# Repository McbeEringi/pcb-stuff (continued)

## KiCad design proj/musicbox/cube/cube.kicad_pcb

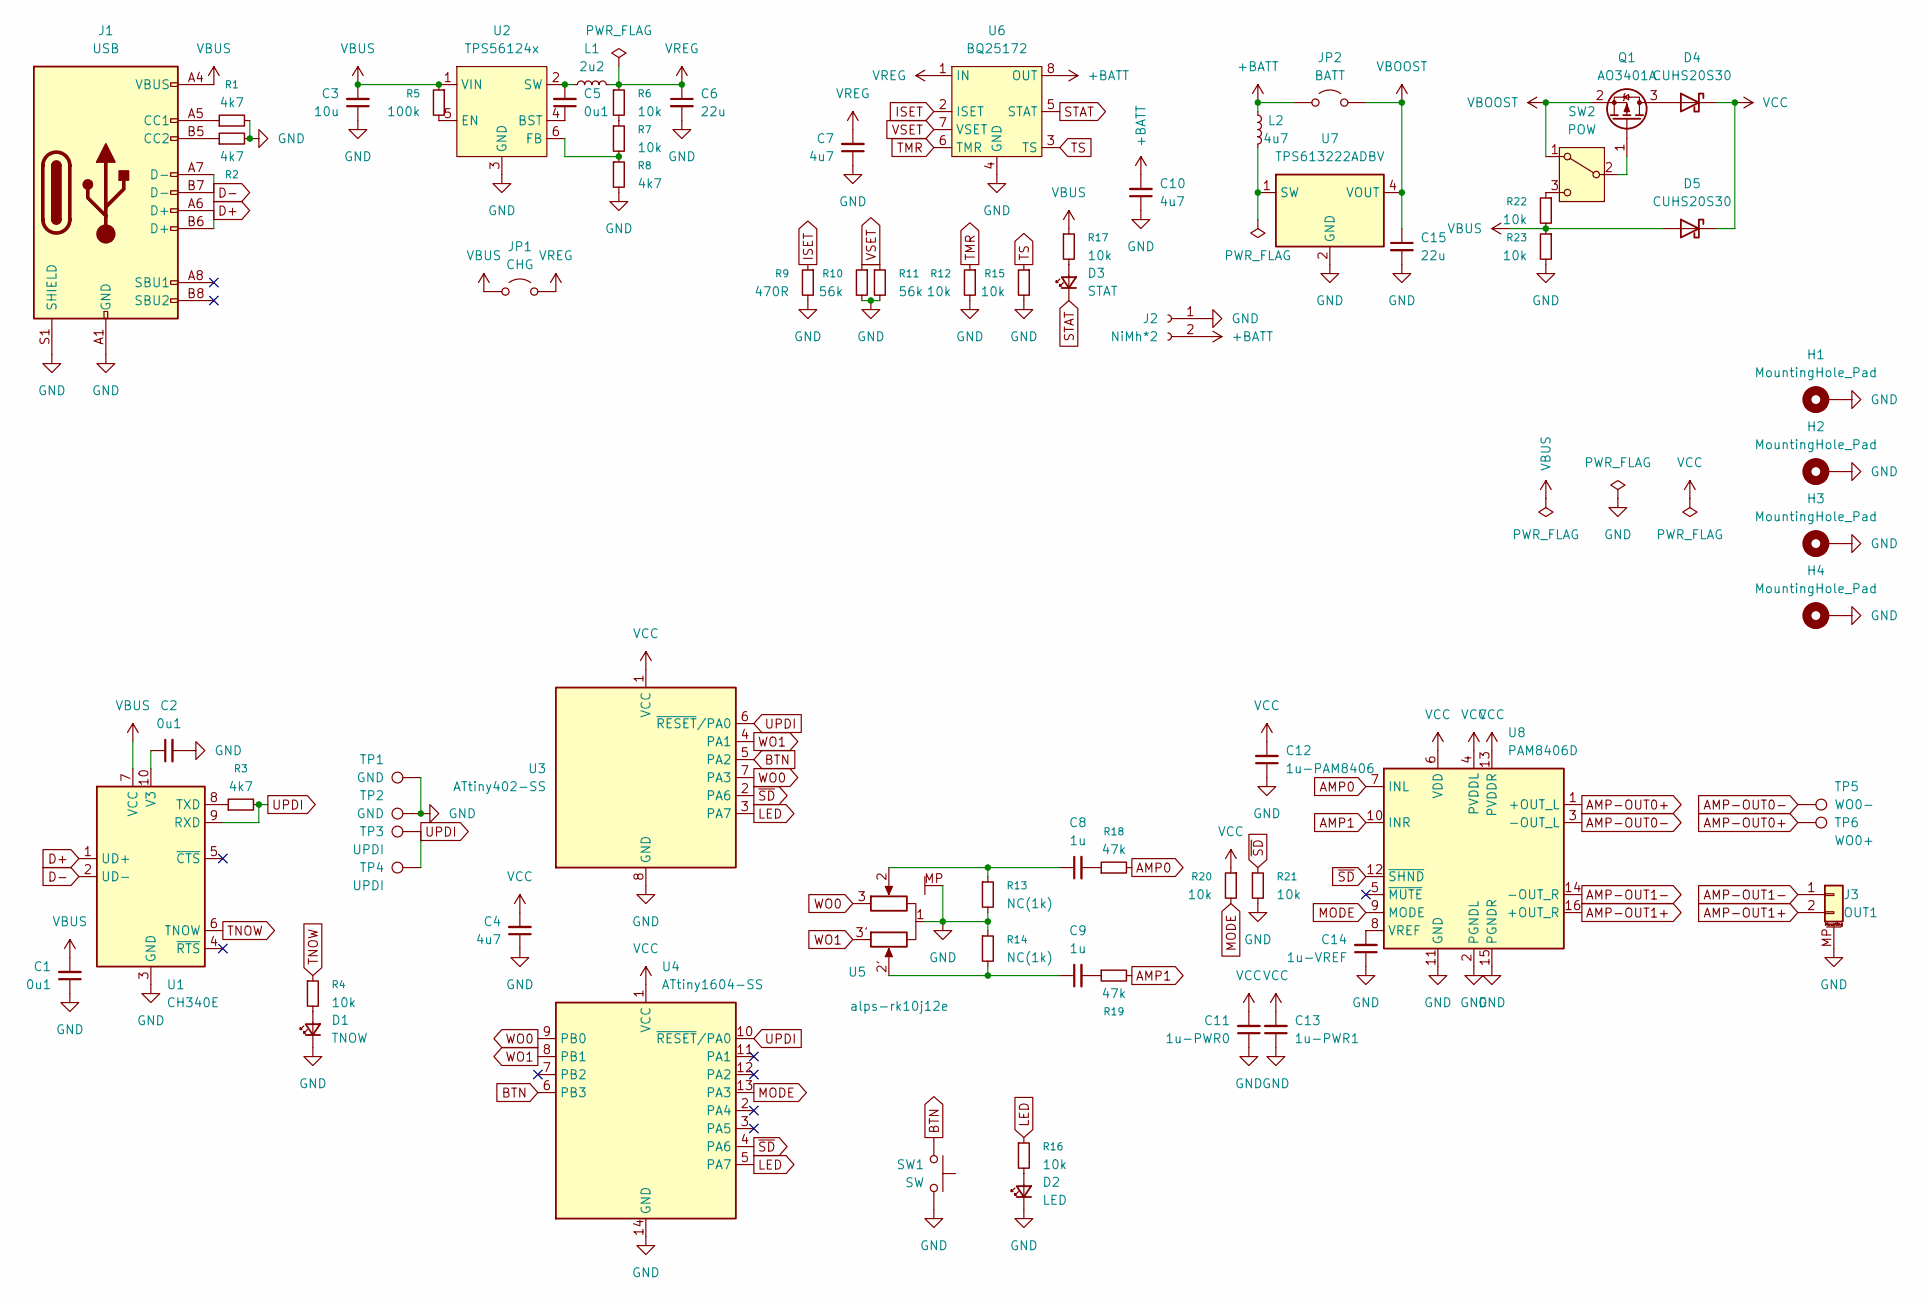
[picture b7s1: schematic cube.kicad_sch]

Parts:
C1, C2, C5: 0u1; C_0603_1608Metric
C3: 10u; C_0603_1608Metric
C4, C7, C10: 4u7; C_0603_1608Metric
C6, C15: 22u; C_0603_1608Metric
C8, C9: 1u; C_0603_1608Metric
C11: 1u-PWR0; C_0603_1608Metric
C12: 1u-PAM8406; C_0603_1608Metric
C13: 1u-PWR1; C_0603_1608Metric
C14: 1u-VREF; C_0603_1608Metric
D1: TNOW; LED_0603_1608Metric
D2: LED; LED_0603_1608Metric
D3: STAT; LED_0603_1608Metric
D4, D5: CUHS20S30; US2H
H1, H2, H3, H4: MountingHole_Pad; MountingHole_3.2mm_M3_Pad
J1: USB; USB_C_Receptacle_GCT_USB4105-xx-A_16P_TopMnt_Horizontal
J2: NiMh*2; JST_XH_B2B-XH-A_1x02_P2.50mm_Vertical
J3: OUT1; JST_ZH_S2B-ZR-SM4A-TF_1x02-1MP_P1.50mm_Horizontal
JP1: CHG; R_0603_1608Metric
JP2: BATT; R_0603_1608Metric
L1: 2u2; L_0805_2012Metric
L2: 4u7; L_1008_2520Metric
Q1: AO3401A; SOT-23
R1, R2, R3, R8: 4k7; R_0603_1608Metric
R4, R6, R7, R12, R15, R16, R17, R20, R21, R22, R23: 10k; R_0603_1608Metric
R5: 100k; R_0603_1608Metric
R9: 470R; R_0603_1608Metric
R10, R11: 56k; R_0603_1608Metric
R13, R14: NC(1k); R_0603_1608Metric
R18, R19: 47k; R_0603_1608Metric
SW1: SW; alps-skr[gp]
SW2: POW; IS-1245T-G
TP1, TP2: GND; TestPoint_Pad_1.5x1.5mm
TP3, TP4: UPDI; TestPoint_Pad_D1.5mm
TP5: WO0-; TestPoint_Pad_1.5x1.5mm
TP6: WO0+; TestPoint_Pad_D1.5mm
U1: CH340E; MSOP-10_3x3mm_P0.5mm
U2: TPS56124x; SOT-563
U3: ATtiny402-SS; SOIC-8_3.9x4.9mm_P1.27mm
U4: ATtiny1604-SS; SOIC-14_3.9x8.7mm_P1.27mm
U5: alps-rk10j12e
U6: BQ25172; WSON-8-1EP_2x2mm_P0.5mm_EP0.9x1.6mm
U7: TPS613222ADBV; SOT-23-5
U8: PAM8406D; SOIC-16_3.9x9.9mm_P1.27mm

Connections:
+BATT: C10.2, J2.2, JP2.1 (A), L2.1, U6.8 (OUT)
AMP0: R18.2, U8.7 (INL)
AMP1: R19.2, U8.10 (INR)
AMP-OUT0+: TP6.1 (1_1), U8.1 (+OUT_L)
AMP-OUT0-: TP5.1 (1_1), U8.3 (-OUT_L)
AMP-OUT1+: J3.2, U8.16 (+OUT_R)
AMP-OUT1-: J3.1, U8.14 (-OUT_R)
BTN: SW1.2, U3.5 (PA2), U4.6 (PB3)
D+: J1.A6 (D+), J1.B6 (D+), U1.1 (UD+)
D-: J1.A7 (D-), J1.B7 (D-), U1.2 (UD-)
GND: C1.1, C2.2, C3.1, C4.1, C6.2, C7.1, C10.1, C11.1, C12.1, C13.1, C14.1, C15.2, D1.1 (K), D2.1 (K), H1.1 (1_1), H2.1 (1_1), H3.1 (1_1), H4.1 (1_1), J1.A1 (GND), J1.A12 (GND), J1.B1 (GND), J1.B12 (GND), J1.S1 (SHIELD), J2.1, J3.MP (MountPin), R1.2, R2.2, R8.2, R9.2, R10.2, R11.2, R12.2, R13.2, R14.1, R15.2, R21.2, R23.2, SW1.1, TP1.1 (1_1), TP2.1 (1_1), U1.3 (GND), U2.3 (GND), U3.8 (GND), U4.14 (GND), U5.1, U5.MP, U6.4 (GND), U6.9 (GND), U7.2 (GND), U8.2 (PGNDL), U8.11 (GND), U8.15 (PGNDR)
ISET: R9.1, U6.2 (ISET)
LED: R16.1, U3.3 (PA7), U4.5 (PA7)
MODE: R20.2, U4.13 (PA3), U8.9 (MODE)
unnamed: C8.1, R13.1, U5.2
unnamed: C8.2, R18.1
unnamed: C9.1, R14.2, U5.2'
unnamed: C9.2, R19.1
unnamed: D1.2 (A), R4.2
unnamed: D2.2 (A), R16.2
unnamed: D3.2 (A), R17.2
unnamed: D4.2 (A), Q1.3 (D)
unnamed: J1.A5 (CC1), R1.1
unnamed: J1.B5 (CC2), R2.1
unnamed: Q1.1 (G), SW2.2 (B)
unnamed: R6.2, R7.1
unnamed: R22.1, SW2.3 (C)
unnamed: R3.1, U1.8 (TXD)
unnamed: C2.1, U1.10 (V3)
unnamed: C5.1, U2.4 (BST)
unnamed: R5.2, U2.5 (EN)
unnamed: R7.2, R8.1, U2.6 (FB)
unnamed: C5.2, L1.1, U2.2 (SW)
unnamed: L2.2, U7.1 (SW)
unnamed: C14.2, U8.8 (VREF)
STAT: D3.1 (K), U6.5 (STAT)
TMR: R12.1, U6.6 (TMR)
TNOW: R4.1, U1.6 (TNOW)
TS: R15.1, U6.3 (TS)
UPDI: R3.2, TP3.1 (1_1), TP4.1 (1_1), U1.9 (RXD), U3.6 (~RESET/PA0), U4.10 (~RESET/PA0)
VBOOST: C15.1, JP2.2 (B), Q1.2 (S), SW2.1 (A), U7.4 (VOUT)
VBUS: C1.2, C3.2, D5.2 (A), J1.A4 (VBUS), J1.A9 (VBUS), J1.B4 (VBUS), J1.B9 (VBUS), JP1.1 (A), R5.1, R17.1, R22.2, R23.1, U1.7 (VCC), U2.1 (VIN)
VCC: C4.2, C11.2, C12.2, C13.2, D4.1 (K), D5.1 (K), R20.1, U3.1 (VCC), U4.1 (VCC), U8.4 (PVDDL), U8.6 (VDD), U8.13 (PVDDR)
VREG: C6.1, C7.2, JP1.2 (B), L1.2, R6.1, U6.1 (IN)
VSET: R10.1, R11.1, U6.7 (VSET)
WO0: U3.7 (PA3), U4.9 (PB0), U5.3
WO1: U3.4 (PA1), U4.8 (PB1), U5.3'
~SD: R21.1, U3.2 (PA6), U4.4 (PA6), U8.12 (~SHND)

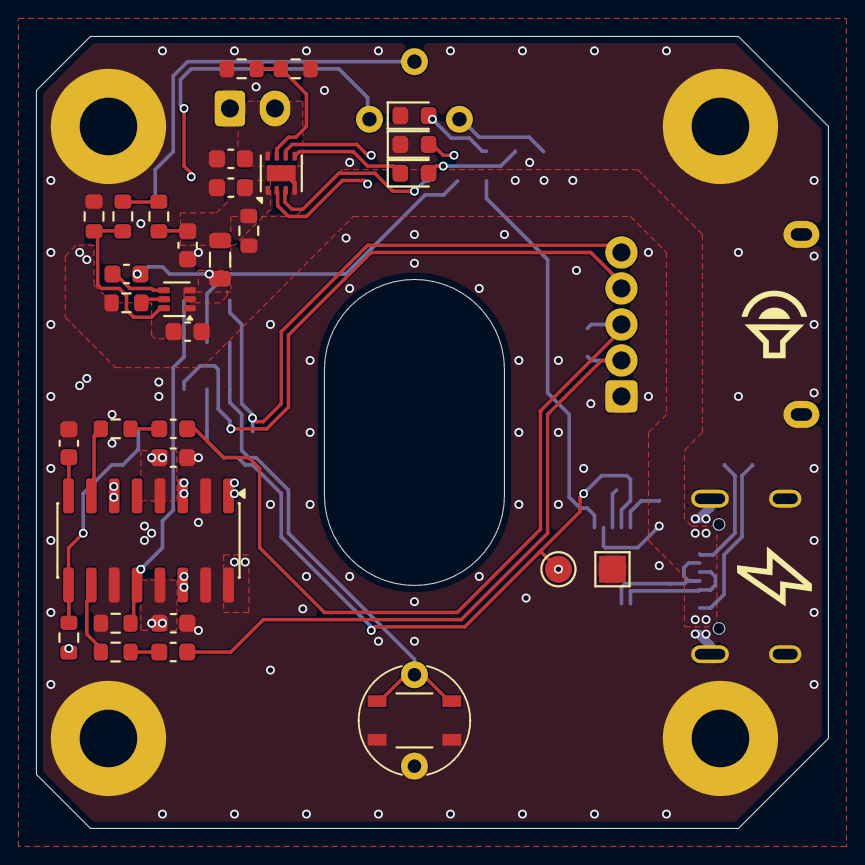
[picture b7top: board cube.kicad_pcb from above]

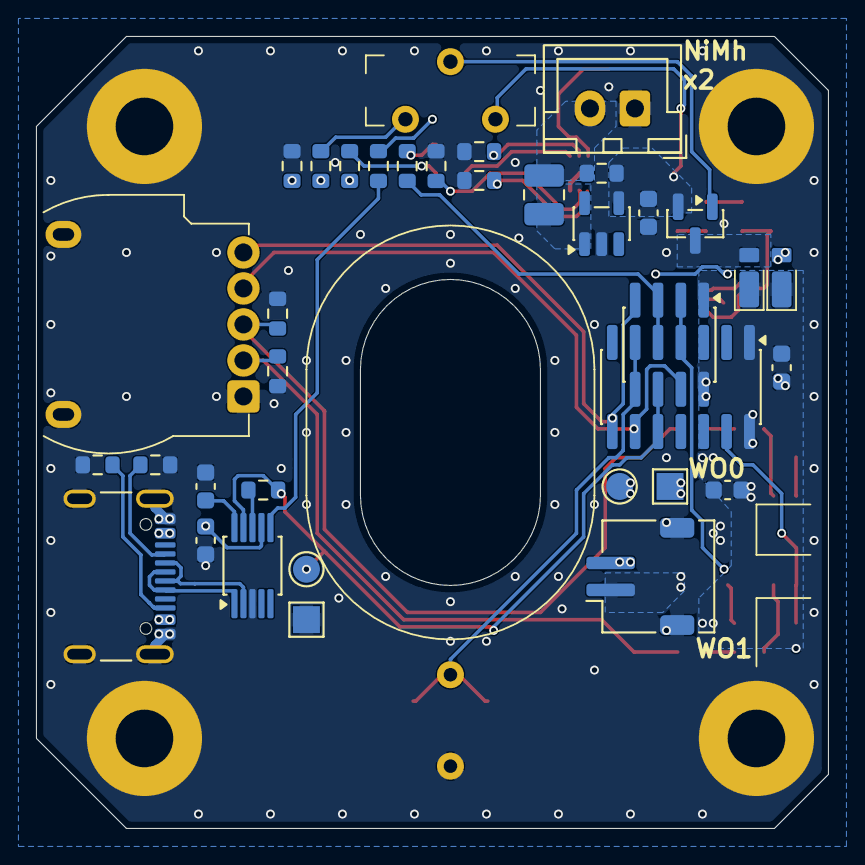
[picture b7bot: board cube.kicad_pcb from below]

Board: 2 copper layers, 44.0 x 44.0 mm, 71 parts (37 on the bottom side), 48 nets.
